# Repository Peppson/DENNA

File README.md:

# radio-nodes

Solar/Battery/USB powered wireless "smarthome" modules, based on the Attiny824 microcontroller.  
Serves as the end-node of [MQTT-radio-gateway](https://github.com/Peppson/MQTT-radio-gateway).   
Written in C++ with PlatformIO.  

&nbsp;
## Project Overview
- Each node is easily configurable to perform various tasks, such as watering plants,  
turn on the coffeemaker, opening blinds, relaying sensor data, etc. 

- Power consumption was the main concern when designing this.   
Nodes consumes ∼`2mA` @ 3.3V in active listening mode, and as low as ∼`3uA` @ 3.3V while deepsleeping!  
Making it possible to power some nodes indefinitely from a small solarpanel.  
Measured and optimized using [Power Profiler Kit II](https://www.nordicsemi.com/Products/Development-hardware/Power-Profiler-Kit-2).  

- This project was primarily made for personal ***"needs"***. But it is open for use by anyone who finds it beneficial.  
Every ***node*** has it's own directory inside `src` with it's own enviroment, selected from `platformio.ini`.

&nbsp;
## Hardware and PCB  
Made a compact PCB integrating a [TP4056](https://www.amazon.com/TP4056/s?k=TP4056) Li-ion/LiPo battery charger, an [nRF24L01+](https://www.amazon.com/s?k=nRF24L01%2B&crid=1VM0GXMUG7ISX&sprefix=nrf24l01%2B%2Caps%2C145&ref=nb_sb_noss_1) radio,   
and the [Attiny824](https://www.mouser.se/ProductDetail/Microchip-Technology/ATTINY824-SSF?qs=pUKx8fyJudA6%2F%2FVSNIlI1w%3D%3D) AVR microcontroller.  

More images in: [📂 _images/](./_images/)  
KiCad files: [📂 _KiCad/](./_KiCad/)  

<details>
<summary>
    Schematic
</summary>  

</details>

<details>
<summary>
    PCB layout 
</summary>     
    
> 2-layer PCB, dimensions 42mm x 31mm.  
> The PCB has 3 sections, configurable based on the node.
> - ***BAT or USB:*** Battery or USB/5V driven.  
> - ***LOAD:*** Components for the "load driver circuit".  

</details>  

<details>
<summary>
    Power consumption in active mode 
</summary>  

> In active mode, the node toggles its radio `on` for 50ms and `off` for 950ms to minimize power usage,    
> halting the CPU between pulses.  
>
> Resulting in an average power draw of ∼2mA @ 3.3V.  

</details>

<details>
<summary>
    Programming
</summary>  

The ATtiny 2-series MCUs have [UPDI](https://onlinedocs.microchip.com/pr/GUID-F626284A-58F0-4C25-A6F3-0EA5054F3E2B-en-US-6/index.html?GUID-D25E0E3F-4FC2-454B-8A2D-C52EAA4EBE81) interface. Which makes it possible to program with only 1 data pin!  
You can see the UPDI pins at the bottom of the PCB. 

I created a simple DIY programmer using an Arduino Nano, to help with uploading firmware.   
More details here [UPDI programmer](https://github.com/Peppson/simple-UPDI-programmer).
</details>

### PCB

### Hardware
> With and without the TP4056 and nRF24L01+ modules. Dimensions 42mm x 31mm.  
> The picture shows a battery/solar-powered node.

&nbsp;
## Nodes 
<details open>
<summary>
    Nodes 1-10: Self watering plants  
</summary>

Uses a 3-5V waterpump and DIY capacative fluid-level sensor.  See link below.  
[Liquid Level Sensing Using Capacitive-to-Digital Converters](https://www.analog.com/en/analog-dialogue/articles/liquid-level-sensing-using-cdcs.html)  

The solar-powered variant uses the TP4056 to charge a Li-ion/LiPo battery.  
While the USB variant skips that step and plugs directly into 5V (with 3.3V LDO onboard).  

#### Node 1 water sensor linearity:    

> Sensor (ADC) reading vs water level in %. 

#### Node 1 hardware:  

> Most of the self-watering plant nodes have the hardware inside a plastic enclosure,   
> which I just hide behind the pots.  
> However, for node 1, I placed all electronics underneath for a pretty decent look.   

&nbsp;  

</details>

<details>
    <summary>
        Node 11: Mocca Master controller
    </summary>

Uses a SG90 servo mounted internally to toggle the `On/Off` button,   
and a hall-effect current sensor, to get the current state.
  
> "Looks pretty neat when the button toggles all by itself :)"   

</details>

&nbsp;

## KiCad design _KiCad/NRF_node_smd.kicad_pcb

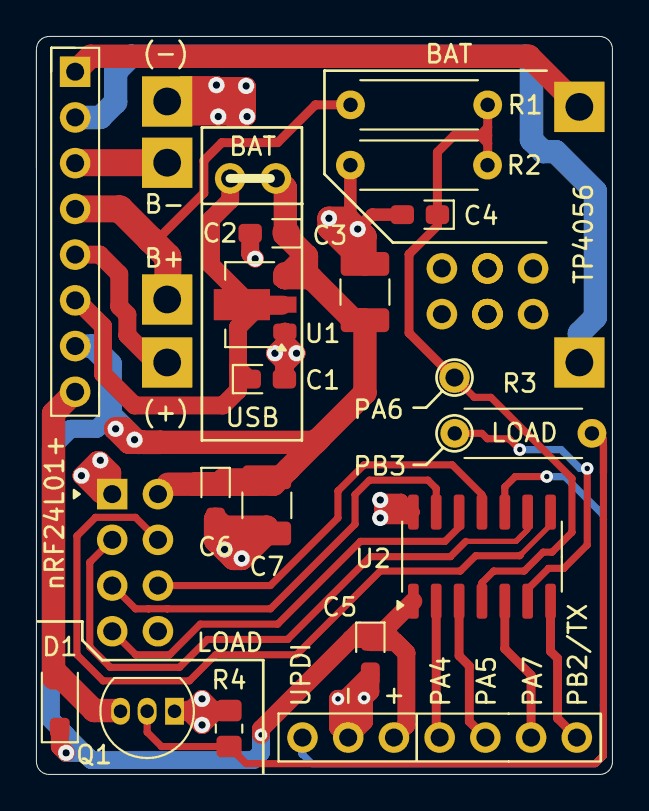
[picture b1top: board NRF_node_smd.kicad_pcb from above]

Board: 2 copper layers, 32.0 x 41.0 mm, 18 parts (0 on the bottom side), 16 nets.

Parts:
C1, C2: 1uf; CP_EIA-2012-15_AVX-P_Pad1.30x1.05mm_HandSolder
C3: 22uF; C_1210_3225Metric_Pad1.33x2.70mm_HandSolder
C4, C5, C6: 100nF; CP_EIA-2012-15_AVX-P_Pad1.30x1.05mm_HandSolder
C7: 10uF; C_1210_3225Metric_Pad1.33x2.70mm_HandSolder
D1: D; D_SOD-123F
J6: Conn_01x06; PinHeader_1x06_P2.54mm_Vertical
Q1: TO-92_Inline
R1: 5.1K; R_Axial_DIN0207_L6.3mm_D2.5mm_P7.62mm_Horizontal
R2: 6.8K; R_Axial_DIN0207_L6.3mm_D2.5mm_P7.62mm_Horizontal
R4: 10K; R_0805_2012Metric_Pad1.20x1.40mm_HandSolder
R8: 0-10K ?; R_Axial_DIN0207_L6.3mm_D2.5mm_P7.62mm_Horizontal
TP4056: TP4056-18650
U1: MCP1700T-3302E/MB; SOT-89-3
U2: ATtiny84A-P; SOIC-14_3.9x8.7mm_P1.27mm
nRF24L01+: NRF24L01_Breakout; nRF24L01_Breakout

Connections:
/CE: U2.9 (PB0), nRF24L01+.3 (CE)
/MISO: U2.12 (PA2), nRF24L01+.7 (MISO)
/MOSI: U2.11 (PA1), nRF24L01+.6 (MOSI)
/SCK: U2.13 (PA3), nRF24L01+.5 (SCK)
/SS: U2.8 (PB1), nRF24L01+.4 (~CSN)
ADC_MEASURE: C4.1, R1.2, R2.2, U2.4 (PA6)
BATTERY_VOLT: R1.1, TP4056.5 (BAT(+))
GND: C1.2, C2.2, C3.2, C4.2, C5.2, C6.2, C7.2, J6.5, Q1.1, R2.1, R4.2, TP4056.3 (GND), U1.1 (GND), U2.14 (GND), nRF24L01+.1 (GND)
LOAD_DRIVER_PIN: R8.1, U2.6 (PB3)
unnamed: D1.2 (A), Q1.3
unnamed: C1.1, U1.2 (VI)
unnamed: Q1.2, R4.1, R8.2
PB4: J6.3, U2.2 (PA4)
PB5: J6.2, U2.3 (PA5)
UPDI: J6.6, U2.10 (~RESET/PA0)
VCC: C2.1, C3.1, C5.1, C6.1, C7.1, D1.1 (K), J6.4, U1.3 (VO), U2.1 (VCC), nRF24L01+.2 (VCC)

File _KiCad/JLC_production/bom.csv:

Designator,Footprint,Quantity,Value,LCSC Part #
"C1, C2",CP_EIA-2012-15_AVX-P_Pad1.30x1.05mm_HandSolder,2,1uf,
C3,1210,1,22uF,
"C4, C5, C6",CP_EIA-2012-15_AVX-P_Pad1.30x1.05mm_HandSolder,3,100nF,
C7,1210,1,10uF,
D1,D_SOD-123F,1,D,
J6,PinHeader_1x06_P2.54mm_Vertical,1,Conn_01x06,
Q1,TO-92_Inline,1,TO-92_Inline,
R1,R_Axial_DIN0207_L6.3mm_D2.5mm_P7.62mm_Horizontal,1,5.1K,
R2,R_Axial_DIN0207_L6.3mm_D2.5mm_P7.62mm_Horizontal,1,6.8K,
R4,0805,1,10K,
R8,R_Axial_DIN0207_L6.3mm_D2.5mm_P7.62mm_Horizontal,1,0-10K ?,
TP4056,TP4056-18650,1,~,
U1,SOT-89-3,1,MCP1700T-3302E/MB ,
U2,SOIC-14_3.9x8.7mm_P1.27mm,1,ATtiny84A-P,
nRF24L01+,nRF24L01_Breakout,1,NRF24L01_Breakout,

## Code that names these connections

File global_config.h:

#pragma once 
#include <Arduino.h>
#include <avr/io.h>
#include <avr/sleep.h>
#include <avr/wdt.h>
#include <avr/interrupt.h>
#include <stdint.h>


// Dev
#define USB_SERIAL_ENABLED 0                                // Serial TX 
#define DEV_RECOVERY_DELAY 1                                // Used for easier code uploading
#define WATCHDOG_ENABLED 1                                  // Onboard Watchdog
#define DEBUG_LOOP_ENABLED 0                                // Enter debug_loop()
#define ADC_CAL_ENABLED 0                                   // Battery ADC calibration
#define PUMP_CAL_ENABLED 0                                  // Water pump calibration
#define SERVO_CAL_ENABLED 0                                 // Servo calibration

// NRF24L01+ radio
constexpr uint8_t RF24_THIS_ADDRESS = NODE_ID;              // Radio address (env var from platformio.ini)
constexpr uint8_t RF24_MASTER_ADDRESS = 0;                  // Address of master (0)
constexpr uint16_t RF24_ON_TIME = 50;                       // Active
constexpr uint16_t RF24_OFF_TIME = 950;                     // Sleeping                                  
constexpr uint8_t RF24_CHANNEL = 120;                       // Channel 1-126 (check with RF24/examples/scanner/scanner.ino) (120)
constexpr uint8_t RF24_PIPE = 1;                            // Pipe address (1)
#define RF24_OUTPUT (RF24_PA_MAX)                           // Output level: RF24_PA_MIN, RF24_PA_LOW, RF24_PA_HIGH, RF24_PA_MAX, ERROR
#define RF24_DATARATE (RF24_250KBPS)                        // Datarate: RF24_2MBPS, RF24_1MBPS, RF24_250KBPS

// Misc
constexpr float SLEEP_RTC_INTERVAL_SECONDS = 64.299;        // Calibrated Average time between RTC interrupts while deepsleeping (s)
constexpr uint8_t WATER_PUMP_RUNTIME_MAX = 10;              // Maximum time the waterpump is allowed to run (s) if a flowerpot node
constexpr uint32_t SERIAL_BAUD_RATE = 9600;                 // TX serial rate

// Message commands
enum MsgCommand : uint16_t {
    REBOOT = 0xFFFF,
    RESEND = 0xFFFE,
    SLEEP = 0xFFFD
};

/*
-------------------------- ATtiny824 Pinout --------------------------                                   

                         VCC  1|o   |14 GND                        
             PWM/ADC --- PA4  2|    |13 PA3 --- RF24 SCK          
             PWM/ADC --- PA5  3|    |12 PA2 --- RF24 MISO  
                 ADC --- PA6  4|    |11 PA1 --- RF24 MOSI           
                 ADC --- PA7  5|    |10 PA0 --- UPDI programming          
           Power I/O --- PB3  6|    |9  PB0 --- RF24 CE          
       TX Serial out --- PB2  7|    |8  PB1 --- RF24 CSN  

----------------------------------------------------------------------
*/
#define PIN_CE                  PIN_PB0         // Nrf24l01 Ce pin
#define PIN_CSN                 PIN_PB1         // Nrf24l01 CSN pin
#define PIN_UPDI                PIN_PB0         // UPDI programming
#define PIN_POWER_IO            PIN_PB3         // Controls the "power circuit"
#define PIN_TX_SERAIL           PIN_PB2         // Serial out   
#define PIN_WATER_SENSOR_OUT    PIN_PA4         // Diy capacitive sensor out    (4)
#define PIN_WATER_SENSOR_IN     PIN_PA5         // Diy capacitive sensor in     (5)                                                              

// Watchdog
#if WATCHDOG_ENABLED
    #define WDT_FEED() __asm__ __volatile__ ("wdr") 
    #define WDT_ENABLE() _PROTECTED_WRITE(WDT.CTRLA, WDT_PERIOD_4KCLK_gc)
    #define WDT_DISABLE() wdt_disable()
#else
    #define WDT_FEED()
    #define WDT_ENABLE()
    #define WDT_DISABLE()
#endif

// Logging
#if USB_SERIAL_ENABLED
    #define log(...) Serial.printf(__VA_ARGS__)
    #define STOP log("\n-----  STOP  ----- \n"); while (1) { WDT_FEED(); delay(1000); }
#else
    #define log(...)
    #define STOP
#endif

// Include selected node's "node_config.h" into global space (a bit hacky?)
#if NODE_ID == 1
    #include "src/01_solar_self_watering_plant/node_config.h"
#elif NODE_ID == 2
    #include "src/02_solar_self_watering_plant/node_config.h"
#elif NODE_ID == 6
    #include "src/06_USB_self_watering_plant/node_config.h"
#elif NODE_ID == 7
    #include "src/07_USB_self_watering_plant/node_config.h"
#elif NODE_ID == 11
    #include "src/11_moccamaster/node_config.h"
#elif NODE_ID == 255 // Debug
    #include "src/255_debug/node_config.h"
#else
    #error "Unknown NODE_ID, check platformio.ini"
#endif

// CALIBRATION true if any of the calibration macros are set
#if DEBUG_LOOP_ENABLED || ADC_CAL_ENABLED || PUMP_CAL_ENABLED || SERVO_CAL_ENABLED
    #define CALIBRATION true
#else 
    #define CALIBRATION false
#endif

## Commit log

2024-07-27 minor watersensor update
